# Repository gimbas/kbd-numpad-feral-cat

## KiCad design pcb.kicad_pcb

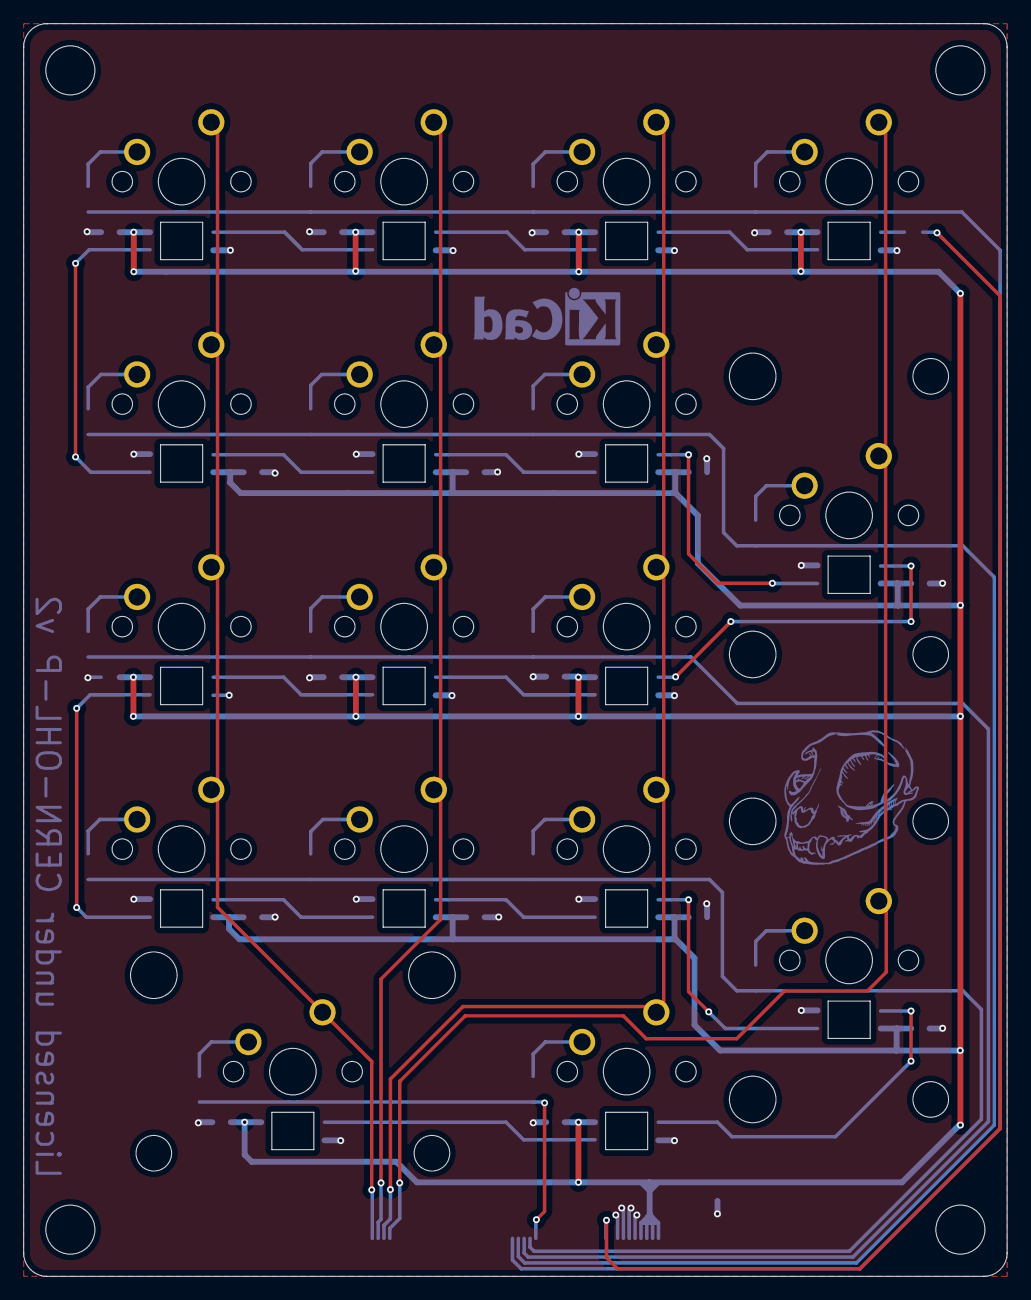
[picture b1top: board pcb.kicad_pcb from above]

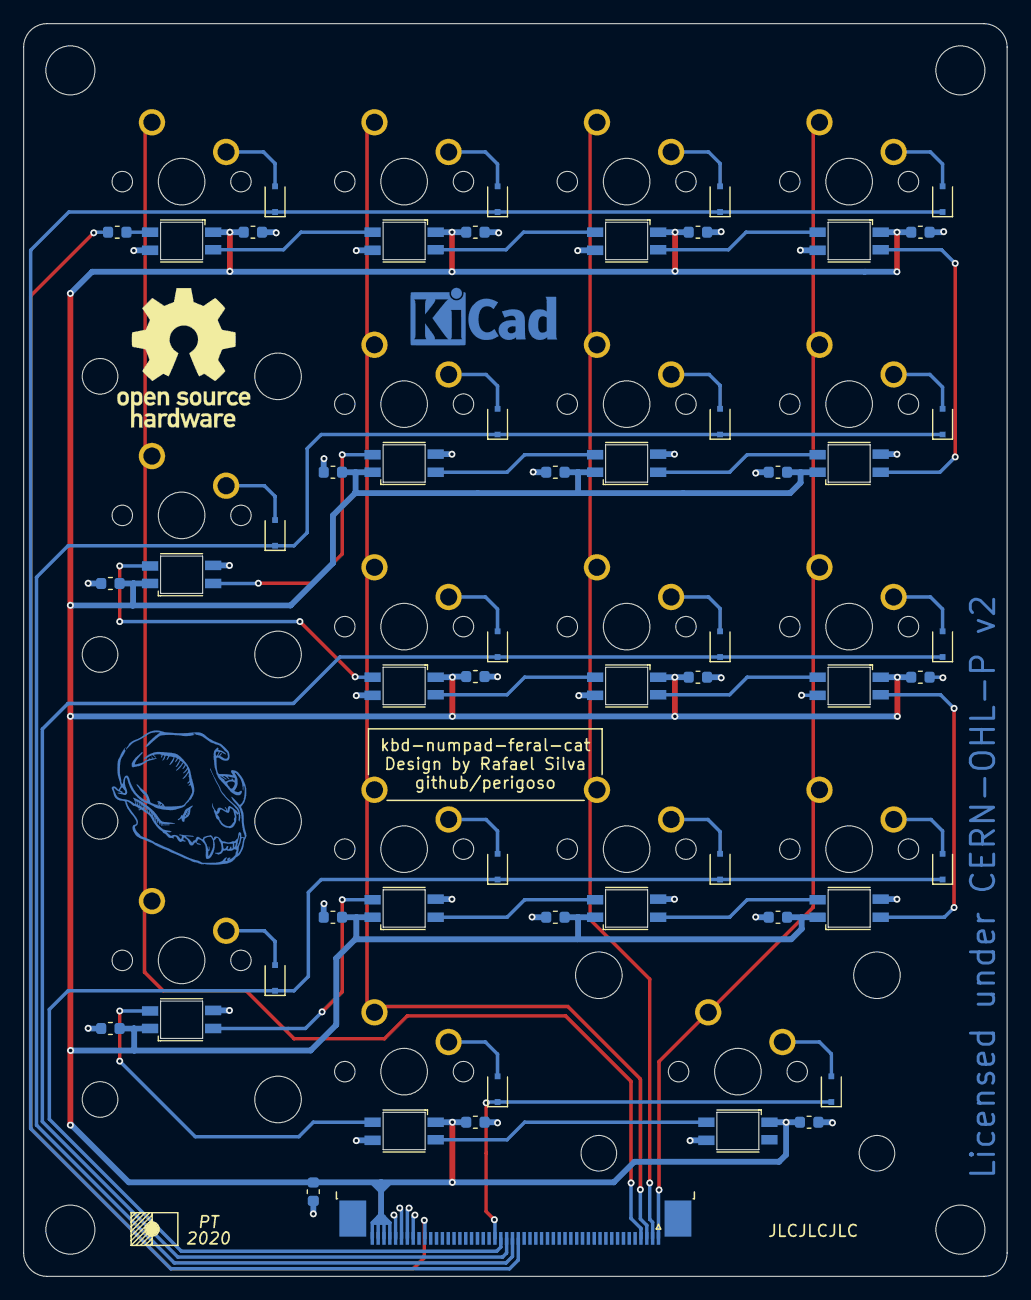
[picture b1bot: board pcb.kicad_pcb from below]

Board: 2 copper layers, 84.2 x 107.3 mm, 71 parts (54 on the bottom side), 46 nets.

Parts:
C1: 10uF; C_0603_1608Metric
C2, C3, C4, C5, C6, C7, C8, C9, C10, C11, C12, C13, C14, C15, C16, C17, C18: 100nF; C_0603_1608Metric
D1, D2, D3, D4, D5, D6, D7, D8, D9, D10, D11, D12, D13, D14, D15, D16, D17: D_Small; D_SOD-323F
D18, D19, D20, D21, D22, D23, D24, D25, D26, D27, D28, D29, D30, D31, D32, D33, D34: SK6812MINI-E
J1: Conn_02x25_Counter_Clockwise; TE_5-1734839-0_1x50-1MP_P0.5mm_Horizontal
R1: 0r; R_0603_1608Metric
SW1, SW2, SW3, SW4, SW6, SW7, SW8, SW9, SW10, SW11, SW12, SW13, SW14, SW15: 1U; MXOnly-1U-NoLED
SW5: 2U; MXOnly-2U-ReversedStabilizers-NoLED
SW16, SW17: 2U; MXOnly-2U-ReversedStabilizers-Rotated-NoLED

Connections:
+5V: C1.1, C2.1, C3.1, C4.1, C5.1, C6.1, C7.1, C8.1, C9.1, C10.1, C11.1, C12.1, C13.1, C14.1, C15.1, C16.1, C17.1, C18.1, D18.1, D19.1, D20.1, D21.1, D22.1, D23.1, D24.1, D25.1, D26.1, D27.1, D28.1, D29.1, D30.1, D31.1, D32.1, D33.1, D34.1, J1.47, J1.48, J1.49, J1.50
/COL0: D1.1, D6.1, D10.1, D15.1, J1.25
/COL1: D2.1, D7.1, D11.1, D16.1, J1.26
/COL2: D3.1, D8.1, D12.1, J1.27
/COL3: D4.1, D9.1, D13.1, D17.1, J1.28
/COL4: D5.1, D14.1, J1.29
/LED_DAT1: J1.41, R1.2
/ROW0: J1.1, SW1.2, SW2.2, SW3.2, SW4.2, SW5.2
/ROW1: J1.2, SW6.2, SW7.2, SW8.2, SW9.2
/ROW2: J1.3, SW10.2, SW11.2, SW12.2, SW13.2, SW14.2
/ROW3: J1.4, SW15.2, SW16.2, SW17.2
/leds/LEDDAT0: D27.4, D32.2
/leds/LEDDAT1: D23.4, D27.2
/leds/LEDDAT2: D18.4, D23.2
/leds/LEDDAT3: D18.2, D19.4
/leds/LEDDAT4: D19.2, D24.4
/leds/LEDDAT5: D24.2, D28.4
/leds/LEDDAT6: D28.2, D33.4
/leds/LEDDAT7: D29.4, D33.2
/leds/LEDDAT8: D25.4, D29.2
/leds/LEDDAT9: D20.4, D25.2
/leds/LEDDAT10: D20.2, D21.4
/leds/LEDDAT11: D21.2, D26.4
/leds/LEDDAT12: D26.2, D30.4
/leds/LEDDAT13: D30.2, D34.4
/leds/LEDDAT14: D31.4, D34.2
/leds/LEDDAT15: D22.4, D31.2
GND: C1.2, C2.2, C3.2, C4.2, C5.2, C6.2, C7.2, C8.2, C9.2, C10.2, C11.2, C12.2, C13.2, C14.2, C15.2, C16.2, C17.2, C18.2, D18.3, D19.3, D20.3, D21.3, D22.3, D23.3, D24.3, D25.3, D26.3, D27.3, D28.3, D29.3, D30.3, D31.3, D32.3, D33.3, D34.3, J1.43, J1.44, J1.45, J1.46
unnamed: D1.2, SW1.1
unnamed: D2.2, SW2.1
unnamed: D3.2, SW3.1
unnamed: D4.2, SW4.1
unnamed: D5.2, SW5.1
unnamed: D6.2, SW6.1
unnamed: D7.2, SW7.1
unnamed: D8.2, SW8.1
unnamed: D9.2, SW9.1
unnamed: D10.2, SW10.1
unnamed: D11.2, SW11.1
unnamed: D12.2, SW12.1
unnamed: D13.2, SW13.1
unnamed: D14.2, SW14.1
unnamed: D15.2, SW15.1
unnamed: D16.2, SW16.1
unnamed: D17.2, SW17.1
unnamed: D32.4, R1.1

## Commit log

2020-08-13 license: added license CERN Open Hardware Licence Version 2
2020-08-13 git: setup ignore files
2020-08-13 libs: added library dependencies not included in official kicad libs
2020-08-13 kicad: project creation
2020-08-13 layout: revA pre-release
2020-08-13 libs: added missing libs
2020-09-06 revA production ready

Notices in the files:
pcb.kicad_pcb:
Licensed under CERN Open Hardware Licence v2 Permissive
Licensed under CERN-OHL-P v2
